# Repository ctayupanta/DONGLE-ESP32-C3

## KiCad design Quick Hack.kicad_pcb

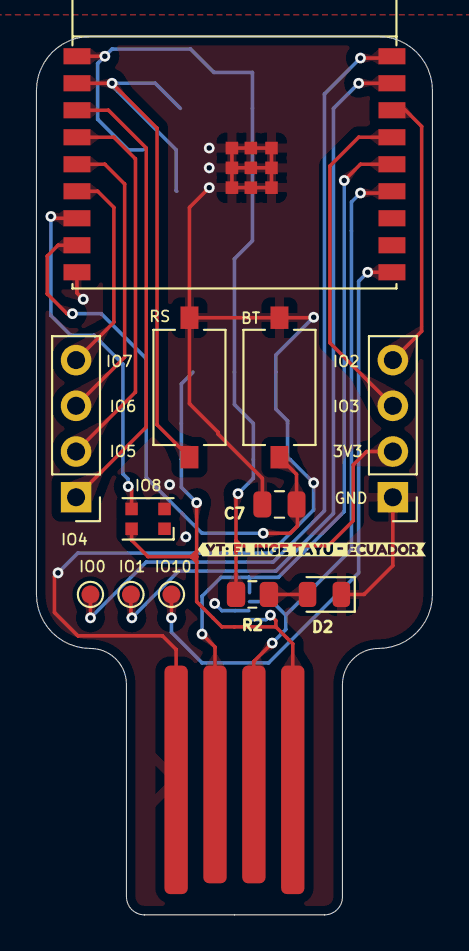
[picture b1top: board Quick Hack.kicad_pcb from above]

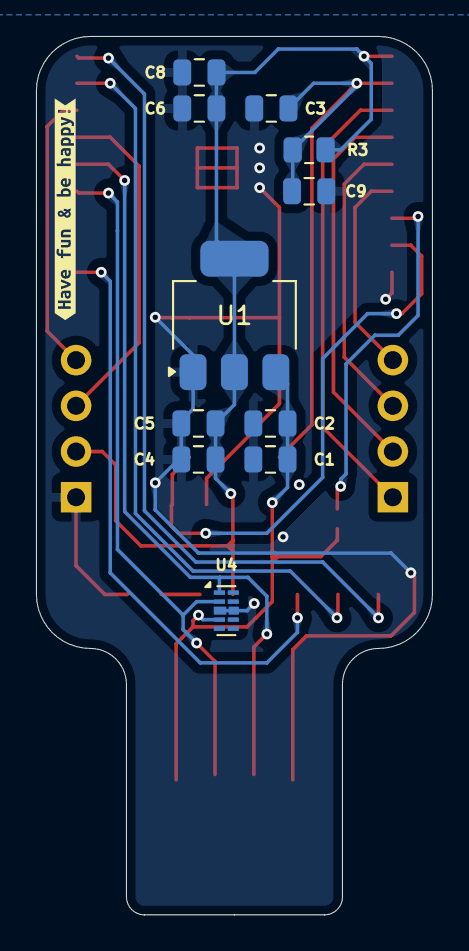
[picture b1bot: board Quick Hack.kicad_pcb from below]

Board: 2 copper layers, 22.0 x 48.8 mm, 26 parts (12 on the bottom side), 18 nets.

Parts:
C1, C5: 10 uF; C_0805_2012Metric
C2, C4: 0.1 uF; C_0805_2012Metric
C3, C6, C7: 0.1uF; C_0805_2012Metric
C8: 10uF; C_0805_2012Metric
C9: 1uF; C_0805_2012Metric
D1: WS2812B-2020; LED_WS2812B-2020_PLCC4_2.0x2.0mm
D2: LED ROJO; LED_0805_2012Metric
J1: Conn_01x04_Pin; USB A CARD
J2, J3: Conn_01x04_Pin; PinHeader_1x04_P2.54mm_Vertical
R2: 330R; R_0805_2012Metric
R3: 10k; R_0805_2012Metric
SW1, SW2: SW_Push; SW_Tactile_SPST_NO_Straight_CK_PTS636Sx25SMTRLFS
TP1, TP2, TP3: TestPoint; TestPoint_Pad_D1.0mm
U1: 3.3v 1A; SOT-223-3_TabPin2
U2: ESP32-C3-WROOM-02
U4: D3V3XA4B10LP; Diodes_UDFN-10_1.0x2.5mm_P0.5mm
kibuzzard-66C7F9C5: G***; kibuzzard-66C7F9C5
kibuzzard-66CE9F7E: G***; kibuzzard-66CE9F7E

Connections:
+3V3: C4.1, C5.1, C6.1, C8.1, J2.2, R2.1, R3.2, U1.2 (VO), U2.1 (3V3)
+5V: C1.1, C2.1, D1.4 (VDD), J1.1, U1.3 (VI), U4.4
BOOT: C7.1, SW2.2, U2.8 (GPIO9)
GND: C1.2, C2.2, C3.2, C4.2, C5.2, C6.2, C7.2, C8.2, C9.2, D1.2 (VSS), D2.1 (K), J1.4, J2.1, SW1.1, SW2.1, U1.1 (GND), U2.9 (GND), U2.19 (GND), U4.3 (VSS), U4.8 (VSS)
IO02: J2.4, U2.16 (GPIO2/ADC1_CH2)
IO03: J2.3, U2.15 (GPIO3/ADC1_CH3)
IO04: J3.1, U2.3 (GPIO4/ADC1_CH4)
IO05: J3.2, U2.4 (GPIO5/ADC2_CH0)
IO06: J3.3, U2.5 (GPIO6)
IO07: J3.4, U2.6 (GPIO7)
IO08: D1.3 (DIN), U2.7 (GPIO8)
unnamed: D2.2 (A), R2.2
unnamed: TP2.1, U2.18 (GPIO0/ADC1_CH0/XTAL_32K_P)
unnamed: TP3.1, U2.17 (GPIO1/ADC1_CH1/XTAL_32K_N)
unnamed: TP1.1, U2.10 (GPIO10)
RESET: C3.1, C9.1, R3.1, SW1.2, U2.2 (EN/CHIP_PU)
USB_D+: J1.3, U2.14 (GPIO19/USB_D+), U4.1
USB_D-: J1.2, U2.13 (GPIO18/USB_D-), U4.2
